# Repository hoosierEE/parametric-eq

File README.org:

* Parseq (Parametric Equalizer)

/(Par)ametric + (s)helving (eq)ualizer ⇒ Parseq/

An equalizer (EQ) effect is an understated workhorse. It expands the capabilities of your existing pedals, can fix sonic problems with surgical precision, or simply add a different color to your palette.

Graphic EQs can't be beat for their easy-to-use interface, but all those sliders take up a lot of space and cutting long slots in an enclosure isn't as DIY-friendly as a design with rotary knobs.

Fully parametric EQs are still EQs but in practice they fill a different niche than a graphic EQ. Rather than constructing a frequency response graph, a fully parametric EQ excels at pinpointing a specific frequency to cut or boost with precision.

[[https://www.falstad.com/afilter/circuitjs.html?cct=$+1+0.000005+5+50+5+50%0A%25+0+20615.097787781793%0AO+1264+208+1312+208+0%0A170+32+144+32+96+3+20+1000+5+0.1%0Aa+288+416+384+416+0+15+-15+1000000%0Aa+512+432+608+432+0+15+-15+1000000%0Aa+656+224+768+224+1+15+-15+1000000%0Aw+656+240+656+272+0%0Ar+656+272+768+272+0+10000%0Aw+768+272+768+224+0%0A174+496+160+400+192+0+10000+0.005+mids+(10k)%0Ar+448+240+272+240+0+3300%0Aw+272+240+272+432+0%0Ag+512+448+512+464+0%0Aw+272+432+288+432+0%0Aw+288+400+288+368+0%0Ar+288+368+384+368+0+10000%0Aw+384+368+384+416+0%0Ar+288+400+176+400+0+1000%0A174+176+400+128+496+0+10000+0.9950000000000001+Q+(10k)%0Ar+128+448+128+352+0+1000%0Ar+448+416+512+416+0+3300%0Aw+512+416+512+368+0%0Ac+512+368+608+368+0+1e-8+0%0Aw+608+368+608+432+0%0Aw+416+384+448+384+0%0Aw+448+384+448+416+0%0Aw+672+400+672+432+0%0Aw+640+400+672+400+0%0Aw+832+384+832+448+0%0Ac+736+384+832+384+0+1e-8+0%0Aw+736+432+736+384+0%0Ar+672+432+736+432+0+3300%0Ag+736+464+736+480+0%0Aa+736+448+832+448+0+15+-15+1000000%0Aw+832+448+832+544+0%0Ar+832+544+288+544+0+10000%0Aw+288+544+288+400+0%0Aw+400+160+400+272+0%0Ar+400+272+656+272+0+10000%0Aw+496+160+768+160+0%0Aw+768+160+768+224+0%0Aw+608+368+608+208+0%0Aw+608+208+656+208+0%0Aw+608+432+608+496+0%0Ar+608+496+272+496+0+10000%0Aw+176+496+272+496+0%0A174+672+432+608+400+0+100000+0.8465+f2+(100k)%0A174+448+416+384+384+0+100000+0.8465+f1+(100k)%0Aa+128+160+240+160+1+15+-15+1000000%0Ac+32+144+80+144+0+3.3e-8+0%0Ar+80+144+80+352+0+1000000%0Ag+80+352+80+384+0%0Aw+128+176+128+208+0%0Ar+128+208+240+208+0+10000%0Aw+240+208+240+160+0%0Ar+128+256+128+304+0+10000%0Ac+128+304+128+352+0+0.000001+0%0Aw+128+352+80+352+0%0Aw+80+144+128+144+0%0Aw+240+160+400+160+0%0Ac+1152+160+1232+160+0+0.00001+0%0Ag+1232+256+1232+272+0%0A174+1232+256+1264+160+0+10000+0.5+level+(10k)%0Aw+656+272+656+320+0%0Ac+656+320+768+320+0+3.3e-10+0%0Aw+768+272+768+320+0%0Ac+128+256+240+256+0+3.3e-10+0%0Aw+240+208+240+256+0%0Aw+128+208+128+256+0%0Aw+448+192+448+240+0%0Aw+272+432+272+496+0%0Aa+1056+160+1152+160+0+15+-15+1000000%0Ag+1056+176+1056+192+0%0Aw+1056+144+1056+112+0%0Ac+1056+112+1152+112+0+1e-10+0%0Aw+1152+112+1152+160+0%0A174+1040+272+1024+208+0+10000+0.5+treble+(10k)%0A174+848+272+864+208+0+10000+0.5+bass+(10k)%0Ar+848+208+848+160+0+2200%0Ar+848+272+848+320+0+2200%0Aw+848+272+784+272+0%0Ac+784+272+784+208+0+1e-7+0%0Aw+784+208+848+208+0%0Ar+864+240+912+240+0+10000%0Ac+912+240+960+240+0+1e-8+0%0Ar+960+240+1024+240+0+3300%0Aw+912+240+912+144+0%0Aw+912+144+1056+144+0%0Aw+1040+208+1040+160+0%0Aw+1040+160+848+160+0%0Aw+848+160+768+160+0%0Aw+848+320+1040+320+0%0Aw+1040+272+1040+320+0%0Aw+1040+320+1152+320+0%0Aw+1152+160+1152+320+0%0Ax+88+496+150+499+0+16+Q+(b10k)%0Ax+396+128+540+131+0+16+mid+boost/cut+(b10k)%0AB+400+368+464+448+2+Box%0AB+624+384+688+464+2+Box%0Ax+485+487+605+490+0+16+freq+(dual+c100k)%0AB+464+464+624+512+2+Box%0Ax+868+284+951+287+0+16+bass+(b10k)%0Ax+1056+268+1145+271+0+16+treble+(b10k)%0Ax+1216+132+1298+135+0+16+level+(a10k)%0Ao+1+16+0+34+5+0.00009765625+0+-1+in%0Ao+0+16+0+34+2.5+0.00009765625+1+-1+out%0A][This design]] takes a lot of inspiration from [[https://bentfishbowl.wixsite.com/electronics/post/core-shaper][Dylan's Core Shaper]], another EQ with a parametric midrange. The Core Shaper is a simpler design (only 4 op-amps required) with a semi-parametric midrange control based on a Wein bridge filter. The mid sweep of the Core Shaper extends from about 310Hz to 3.2kHz. The Q in the Core Shaper is switchable from low (~0.3) to high (~0.8)

#+caption: Parseq schematic
[[file:./parseq.png]]

NOTE: table contains *simulated* values

| mid parameter  | Core Shaper | Parseq |
|----------------+-------------+--------|
| min freq (Hz)  |         311 |    155 |
| max freq (Hz)  |        3220 |   4180 |
| min Q          |         0.3 |    0.3 |
| max Q          |         0.8 |    2.4 |
| max boost (dB) |          16 |     15 |
| max cut (dB)   |         -16 |    -16 |

By contrast, the Parseq uses a state variable filter for the midrange which gives it a wider bandwidth sweep as well as continuous control over the Q factor instead of a 2-mode switch. The downside of this design is it requires more components.

Besides the mid filter, the Parseq takes nearly all of its design cues from the Core Shaper:

1. input fixed gain stage
2. parametric midrange
3. Baxandall treble/bass shelving filters
4. passive output attenuator for volume control

Use the Parseq when you want more precision than the Core Shaper and don't mind the extra circuit complexity.

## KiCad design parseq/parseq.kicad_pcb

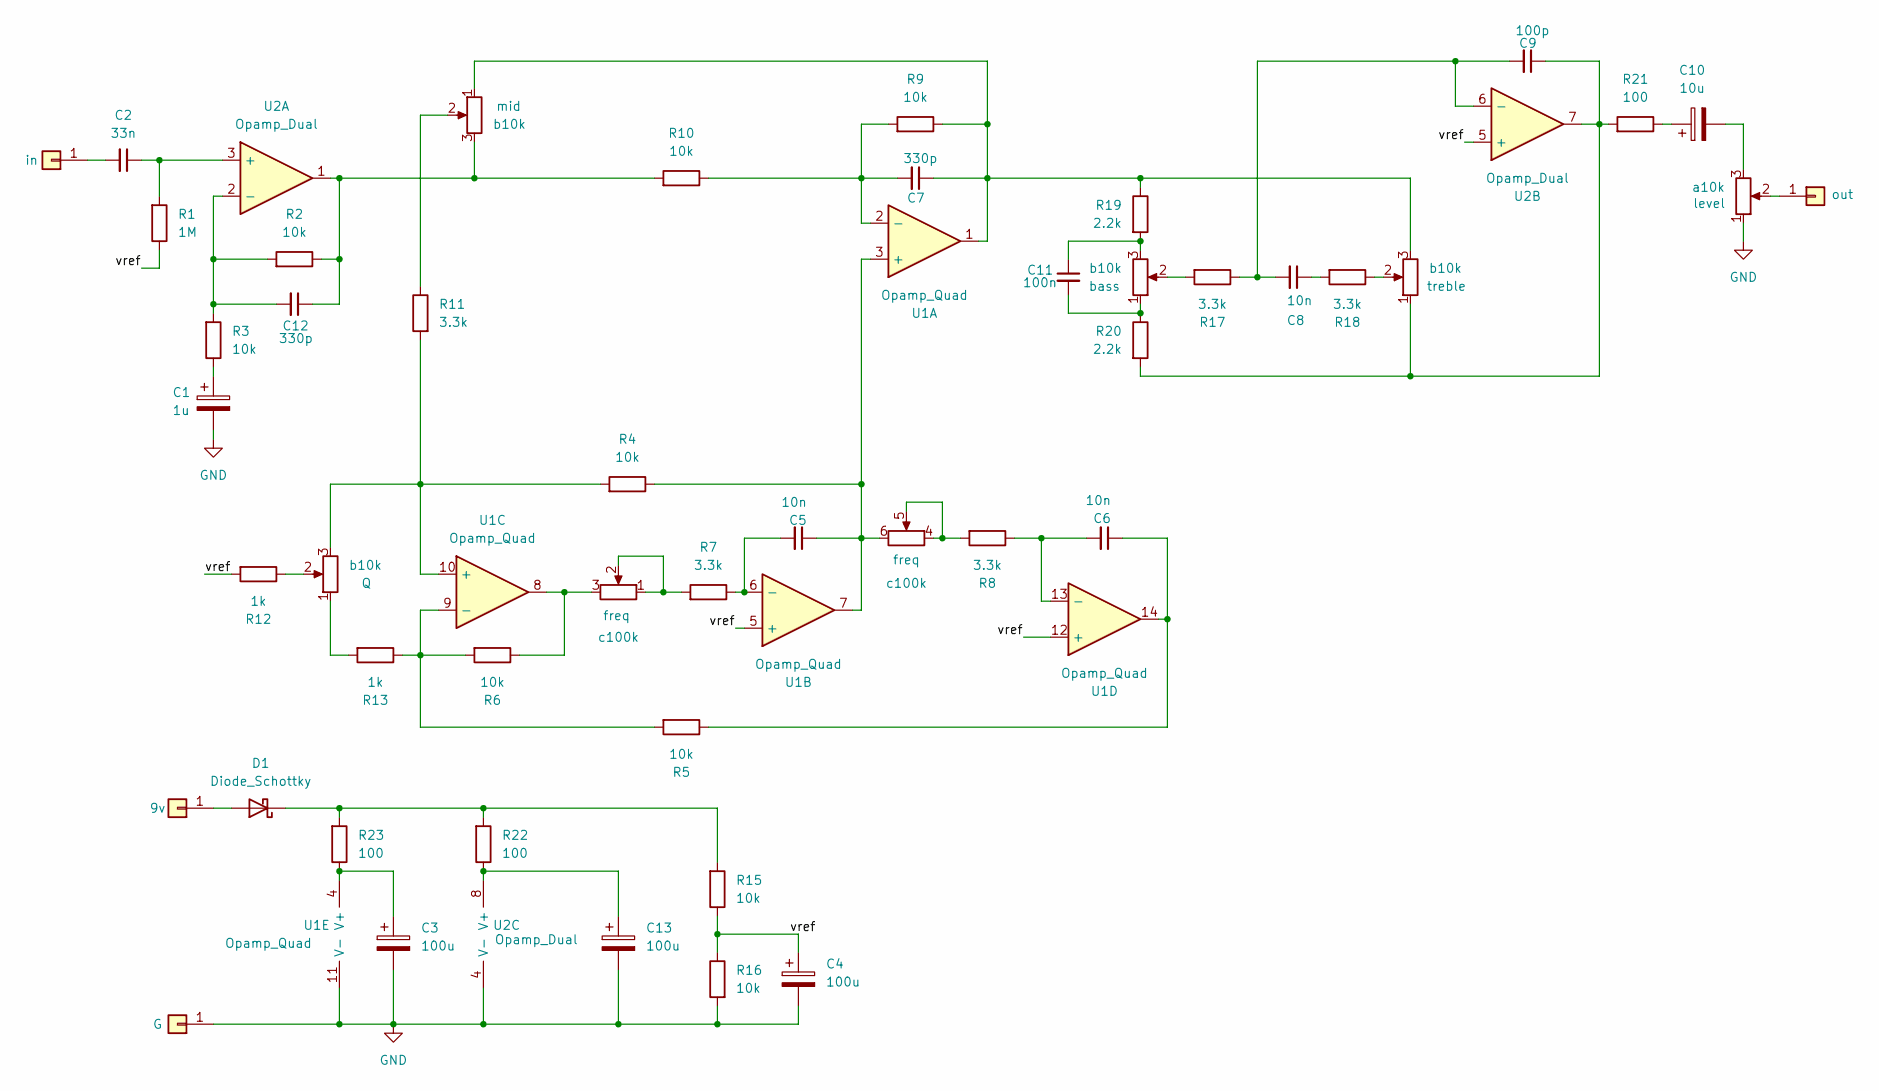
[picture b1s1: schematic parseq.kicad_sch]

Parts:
C1: 1u; CP_ELCO_1x2_S
C2: 33n; C_CERAMIC_1x2
C3, C4, C13: 100u; CP_ELCO_1x2_S
C5, C6, C8: 10n; C_CERAMIC_1x2
C7, C12: 330p; C_CERAMIC_1x2
C9: 100p; C_CERAMIC_1x2
C10: 10u; CP_ELCO_1x2_S
C11: 100n; C_CERAMIC_1x2
D1: Diode_Schottky; D_A-405_P7.62mm_Horizontal
J1, J2, J3, J4: Conn_01x01; PAD_1_std_sqr
R1: 1M; R_1x4
R2, R3, R4, R5, R6, R9, R10, R15, R16: 10k; R_1x4
R7, R8, R11, R17, R18: 3.3k; R_1x4
R12, R13: 1k; R_1x4
R19, R20: 2.2k; R_1x4
R21, R22, R23: 100; R_1x4
RV1: c100k; Potentiometer_Alpha_RD902F-40-00D_Dual_Vertical
RV2, RV3, RV4, RV5: b10k; Potentiometer_Alpha_RD901F-40-00D_Single_Vertical
RV6: a10k; Potentiometer_Alpha_RD901F-40-00D_Single_Vertical
U1: Opamp_Quad; DIP-14
U2: Opamp_Dual; DIP-8

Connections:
/vref: C4.1, R1.2, R12.1, R15.2, R16.2, U1.5 (+), U1.12 (+), U2.5 (+)
GND: C1.2, C3.2, C4.2, C13.2, J2.1, R16.1, RV6.1, U1.11 (V-), U2.4 (V-)
unnamed: C1.1, R3.2
unnamed: C6.1, R5.2, U1.14
unnamed: C7.1, R9.2, R19.2, RV2.1, RV5.3, U1.1
unnamed: C8.1, R18.1
unnamed: C9.1, R20.1, R21.1, RV5.1, U2.7
unnamed: C10.1, R21.2
unnamed: C10.2, RV6.3
unnamed: C11.1, R19.1, RV4.3
unnamed: C11.2, R20.2, RV4.1
unnamed: C12.1, R2.2, R10.1, RV2.3, U2.1
unnamed: D1.2 (A), J1.1
unnamed: D1.1 (K), R15.1, R22.1, R23.1
unnamed: C2.2, J3.1
unnamed: J4.1, RV6.2
unnamed: R8.1, RV1.4, RV1.5
unnamed: R11.2, RV2.2
unnamed: R12.2, RV3.2
unnamed: R13.1, RV3.1
unnamed: R17.1, RV4.2
unnamed: R18.2, RV5.2
unnamed: R7.1, RV1.1 (4), RV1.2 (5)
unnamed: R6.2, RV1.3 (6), U1.8
unnamed: C5.1, R4.2, RV1.6, U1.3 (+), U1.7
unnamed: C7.2, R9.1, R10.2, U1.2 (-)
unnamed: C5.2, R7.2, U1.6 (-)
unnamed: R4.1, R11.1, RV3.3, U1.10 (+)
unnamed: R5.1, R6.1, R13.2, U1.9 (-)
unnamed: C6.2, R8.2, U1.13 (-)
unnamed: C3.1, R23.2, U1.4 (V+)
unnamed: C2.1, R1.1, U2.3 (+)
unnamed: C12.2, R2.1, R3.1, U2.2 (-)
unnamed: C8.2, C9.2, R17.2, U2.6 (-)
unnamed: C13.1, R22.2, U2.8 (V+)

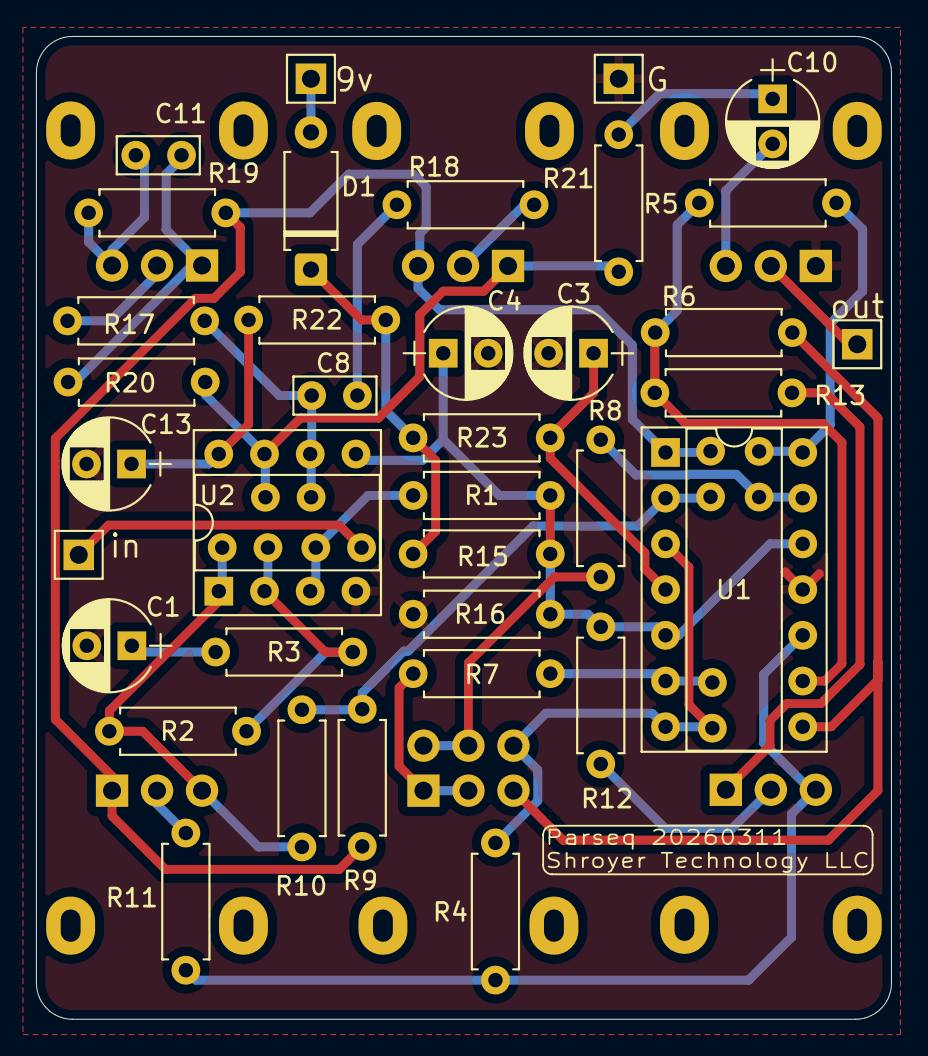
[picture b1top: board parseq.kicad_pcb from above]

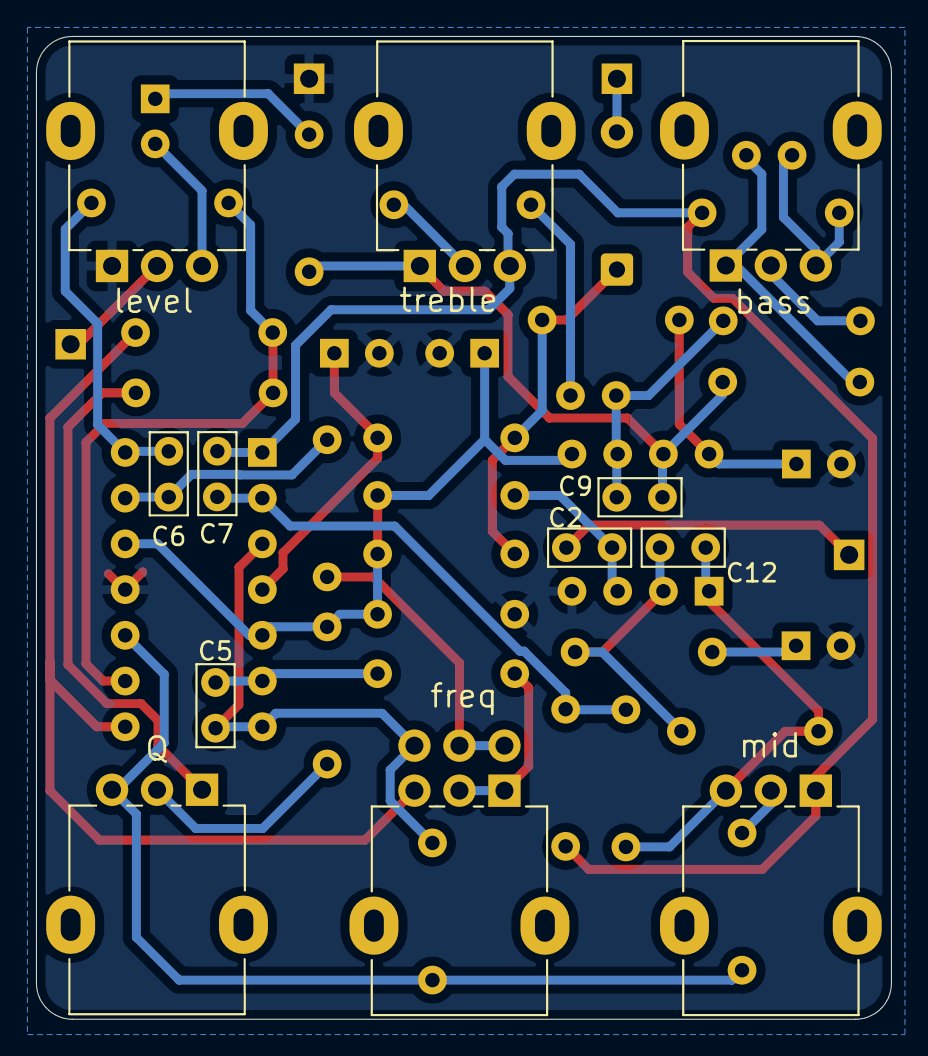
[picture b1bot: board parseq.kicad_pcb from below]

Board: 2 copper layers, 47.5 x 54.6 mm, 48 parts (12 on the bottom side), 35 nets.

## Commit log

2026-03-04 update gitignore
2026-03-04 update link
2026-03-09 all nets routed
2026-03-09 retcon the name
2026-03-11 update board
2026-03-11 shorter tracks
2026-03-12 add name and version to silkscreen
2026-04-21 snapshot
